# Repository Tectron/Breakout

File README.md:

Terrible Fire Break Out Boards
=================================

* 68020 - PGA114 Breakout

You may get any PCB manufacturer to produce the board for you. The board is 2-layer. I recommend these dirtypcbs links...

http://dirtypcbs.com/view.php?share=26129&accesskey=53f7f219ee0d339a3d1a7b1910aeaeed

* 68030 - PGA128 Breakout

You may get any PCB manufacturer to produce the board for you. The board is 2-layer. I recommend these dirtypcbs links...

http://dirtypcbs.com/view.php?share=28380&accesskey=9c851266aeee43fccca2846767b09b1c

* Libraries

The terriblefire.lbr file contains the following parts :-

XC9572XL-VQ64 (unverfied)

XC95144XL-TQ100 (unverified)

MC68SEC000-QFP64 (unverfied)

These parts are free to use but come with absolutely NO WARRANTY and in many cases have not been verified. 

* Tools

The following GPL tools are available.

54600.py - (Captures the output of a 56400 series scope and writes the output to a VCD file).

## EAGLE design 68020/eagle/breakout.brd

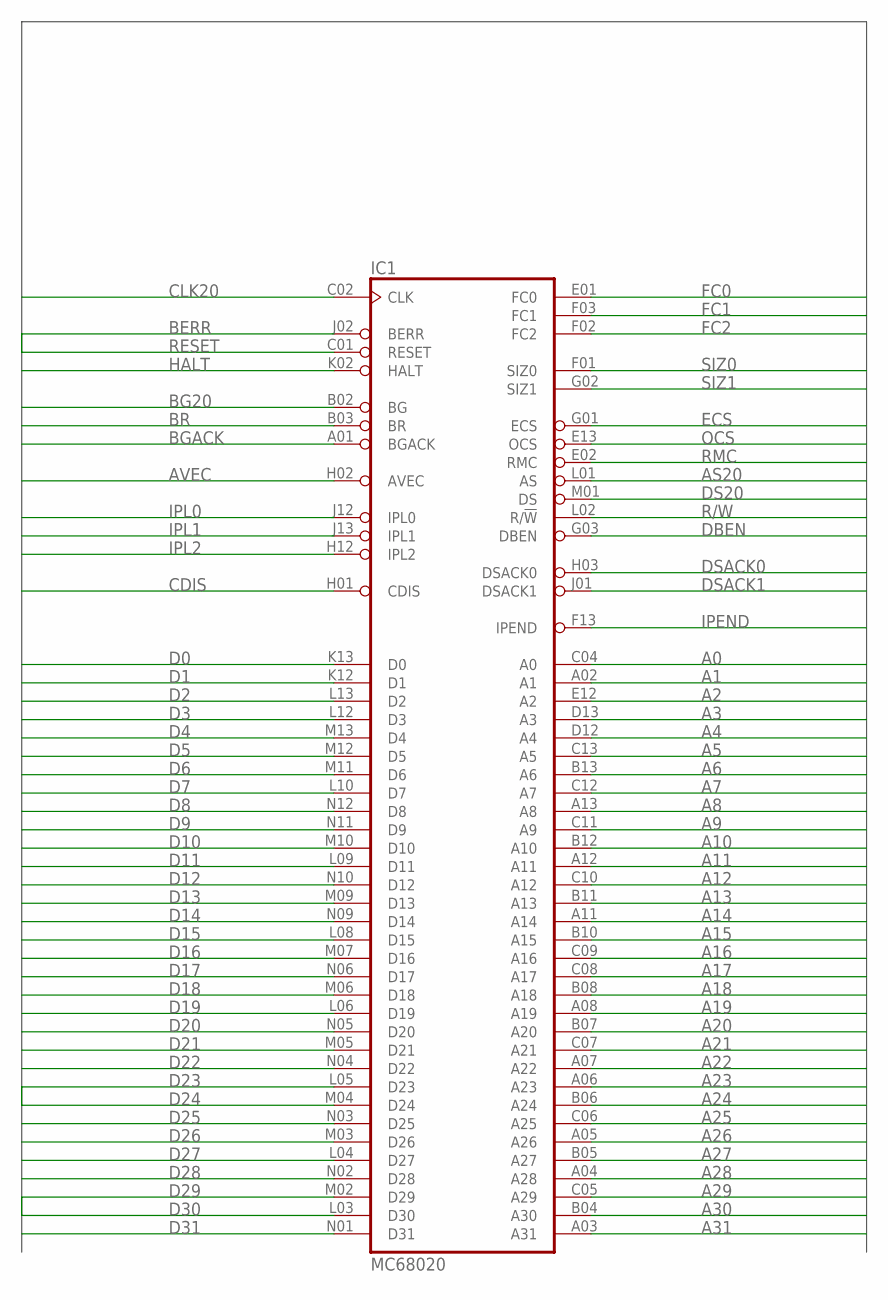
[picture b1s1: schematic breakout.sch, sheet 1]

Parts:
IC1: MC68020; MPGA114

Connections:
A0: IC1.C04 (A0); also elsewhere on the board
A1: IC1.A02 (A1); also elsewhere on the board
A2: IC1.E12 (A2); also elsewhere on the board
A3: IC1.D13 (A3); also elsewhere on the board
A4: IC1.D12 (A4); also elsewhere on the board
A5: IC1.C13 (A5); also elsewhere on the board
A6: IC1.B13 (A6); also elsewhere on the board
A7: IC1.C12 (A7); also elsewhere on the board
A8: IC1.A13 (A8); also elsewhere on the board
A9: IC1.C11 (A9); also elsewhere on the board
A10: IC1.B12 (A10); also elsewhere on the board
A11: IC1.A12 (A11); also elsewhere on the board
A12: IC1.C10 (A12); also elsewhere on the board
A13: IC1.B11 (A13); also elsewhere on the board
A14: IC1.A11 (A14); also elsewhere on the board
A15: IC1.B10 (A15); also elsewhere on the board
A16: IC1.C09 (A16); also elsewhere on the board
A17: IC1.C08 (A17); also elsewhere on the board
A18: IC1.B08 (A18); also elsewhere on the board
A19: IC1.A08 (A19); also elsewhere on the board
A20: IC1.B07 (A20); also elsewhere on the board
A21: IC1.C07 (A21); also elsewhere on the board
A22: IC1.A07 (A22); also elsewhere on the board
A23: IC1.A06 (A23); also elsewhere on the board
A24: IC1.B06 (A24); also elsewhere on the board
A25: IC1.C06 (A25); also elsewhere on the board
A26: IC1.A05 (A26); also elsewhere on the board
A27: IC1.B05 (A27); also elsewhere on the board
A28: IC1.A04 (A28); also elsewhere on the board
A29: IC1.C05 (A29); also elsewhere on the board
A30: IC1.B04 (A30); also elsewhere on the board
A31: IC1.A03 (A31); also elsewhere on the board
AS20: IC1.L01 (AS); also elsewhere on the board
AVEC: IC1.H02 (AVEC); also elsewhere on the board
BERR: IC1.J02 (BERR); also elsewhere on the board
BG20: IC1.B02 (BG); also elsewhere on the board
BGACK: IC1.A01 (BGACK); also elsewhere on the board
BR: IC1.B03 (BR); also elsewhere on the board
CDIS: IC1.H01 (CDIS); also elsewhere on the board
CLK20: IC1.C02 (CLK); also elsewhere on the board
D0: IC1.K13 (D0); also elsewhere on the board
D1: IC1.K12 (D1); also elsewhere on the board
D2: IC1.L13 (D2); also elsewhere on the board
D3: IC1.L12 (D3); also elsewhere on the board
D4: IC1.M13 (D4); also elsewhere on the board
D5: IC1.M12 (D5); also elsewhere on the board
D6: IC1.M11 (D6); also elsewhere on the board
D7: IC1.L10 (D7); also elsewhere on the board
D8: IC1.N12 (D8); also elsewhere on the board
D9: IC1.N11 (D9); also elsewhere on the board
D10: IC1.M10 (D10); also elsewhere on the board
D11: IC1.L09 (D11); also elsewhere on the board
D12: IC1.N10 (D12); also elsewhere on the board
D13: IC1.M09 (D13); also elsewhere on the board
D14: IC1.N09 (D14); also elsewhere on the board
D15: IC1.L08 (D15); also elsewhere on the board
D16: IC1.M07 (D16); also elsewhere on the board
D17: IC1.N06 (D17); also elsewhere on the board
D18: IC1.M06 (D18); also elsewhere on the board
D19: IC1.L06 (D19); also elsewhere on the board
D20: IC1.N05 (D20); also elsewhere on the board
D21: IC1.M05 (D21); also elsewhere on the board
D22: IC1.N04 (D22); also elsewhere on the board
D23: IC1.L05 (D23); also elsewhere on the board
D24: IC1.M04 (D24); also elsewhere on the board
D25: IC1.N03 (D25); also elsewhere on the board
D26: IC1.M03 (D26); also elsewhere on the board
D27: IC1.L04 (D27); also elsewhere on the board
D28: IC1.N02 (D28); also elsewhere on the board
D29: IC1.M02 (D29); also elsewhere on the board
D30: IC1.L03 (D30); also elsewhere on the board
D31: IC1.N01 (D31); also elsewhere on the board
DBEN: IC1.G03 (DBEN); also elsewhere on the board
DS20: IC1.M01 (DS); also elsewhere on the board
DSACK0: IC1.H03 (DSACK0); also elsewhere on the board
DSACK1: IC1.J01 (DSACK1); also elsewhere on the board
ECS: IC1.G01 (ECS); also elsewhere on the board
FC0: IC1.E01 (FC0); also elsewhere on the board
FC1: IC1.F03 (FC1); also elsewhere on the board
FC2: IC1.F02 (FC2); also elsewhere on the board
GND: IC1.A10 (GND), IC1.B01 (GND), IC1.B09 (GND), IC1.C03 (GND), IC1.F12 (GND), IC1.G12 (GND), IC1.H13 (GND), IC1.J03 (GND), IC1.K01 (GND), IC1.K03 (GND), IC1.L07 (GND), IC1.L11 (GND), IC1.N07 (GND); also elsewhere on the board
HALT: IC1.K02 (HALT); also elsewhere on the board
IPEND: IC1.F13 (IPEND); also elsewhere on the board
IPL0: IC1.J12 (IPL0); also elsewhere on the board
IPL1: IC1.J13 (IPL1); also elsewhere on the board
IPL2: IC1.H12 (IPL2); also elsewhere on the board
OCS: IC1.E13 (OCS); also elsewhere on the board
R/W: IC1.L02 (R/!W); also elsewhere on the board
RESET: IC1.C01 (RESET); also elsewhere on the board
RMC: IC1.E02 (RMC); also elsewhere on the board
SIZ0: IC1.F01 (SIZ0); also elsewhere on the board
SIZ1: IC1.G02 (SIZ1); also elsewhere on the board
VCC: IC1.A09 (VCC), IC1.D01 (VCC), IC1.D02 (VCC), IC1.D03 (VCC), IC1.E03 (VCC), IC1.G11 (VCC), IC1.G13 (VCC), IC1.M08 (VCC), IC1.N08 (VCC), IC1.N13 (VCC); also elsewhere on the board

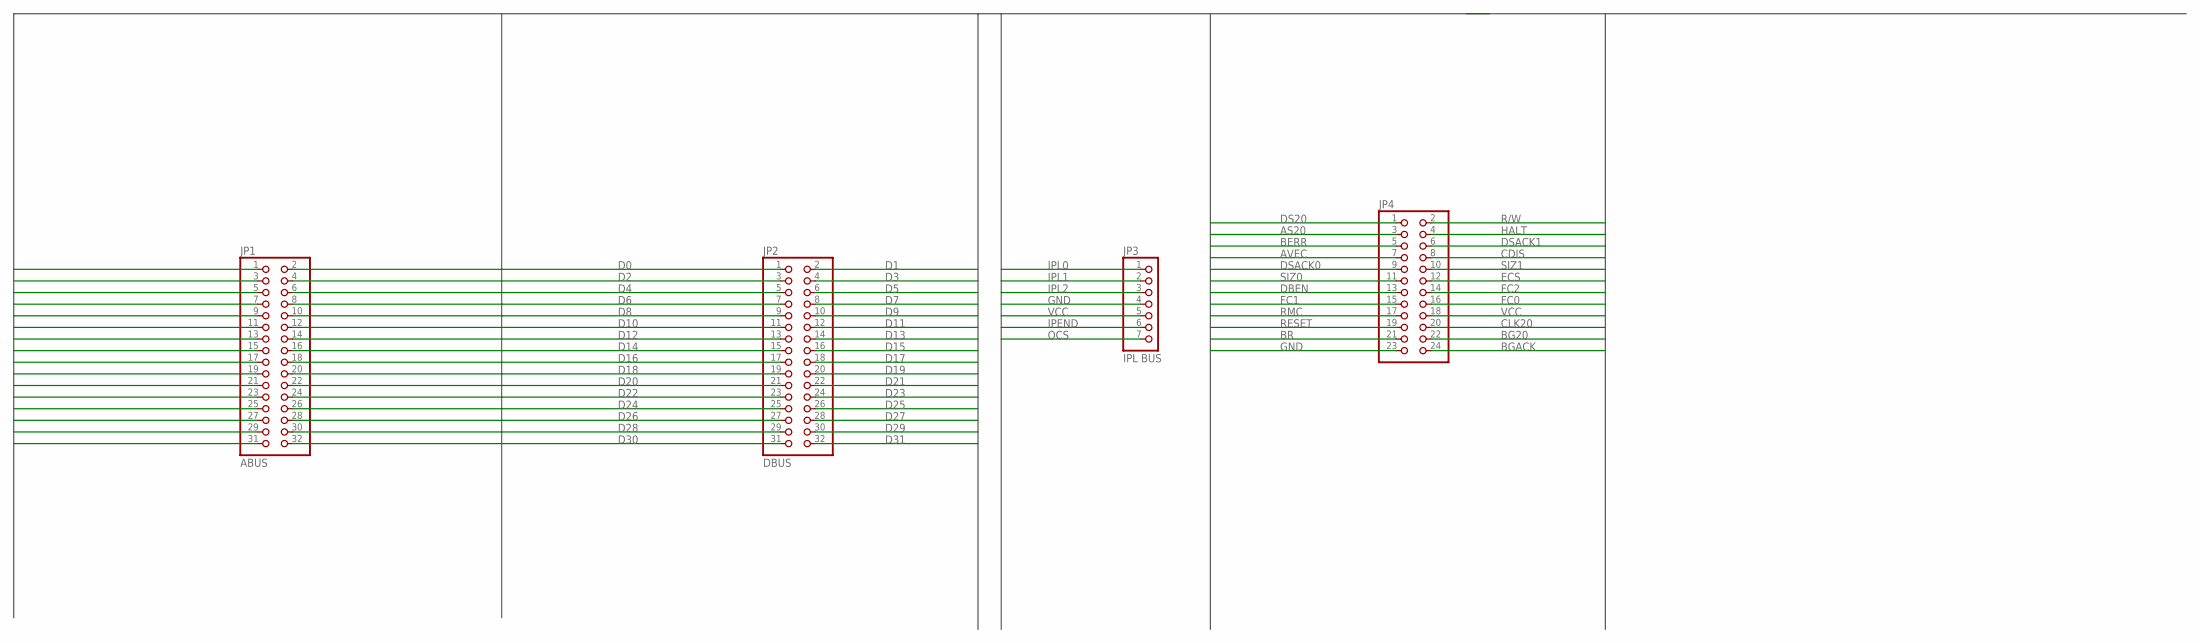
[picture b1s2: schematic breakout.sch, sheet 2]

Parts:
JP1: ABUS; 2X16
JP2: DBUS; 2X16
JP3: IPL BUS; 1X07
JP4: PINHD-2X12; 2X12

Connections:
A0: JP1.1; also elsewhere on the board
A1: JP1.2; also elsewhere on the board
A2: JP1.3; also elsewhere on the board
A3: JP1.4; also elsewhere on the board
A4: JP1.5; also elsewhere on the board
A5: JP1.6; also elsewhere on the board
A6: JP1.7; also elsewhere on the board
A7: JP1.8; also elsewhere on the board
A8: JP1.9; also elsewhere on the board
A9: JP1.10; also elsewhere on the board
A10: JP1.11; also elsewhere on the board
A11: JP1.12; also elsewhere on the board
A12: JP1.13; also elsewhere on the board
A13: JP1.14; also elsewhere on the board
A14: JP1.15; also elsewhere on the board
A15: JP1.16; also elsewhere on the board
A16: JP1.17; also elsewhere on the board
A17: JP1.18; also elsewhere on the board
A18: JP1.19; also elsewhere on the board
A19: JP1.20; also elsewhere on the board
A20: JP1.21; also elsewhere on the board
A21: JP1.22; also elsewhere on the board
A22: JP1.23; also elsewhere on the board
A23: JP1.24; also elsewhere on the board
A24: JP1.25; also elsewhere on the board
A25: JP1.26; also elsewhere on the board
A26: JP1.27; also elsewhere on the board
A27: JP1.28; also elsewhere on the board
A28: JP1.29; also elsewhere on the board
A29: JP1.30; also elsewhere on the board
A30: JP1.31; also elsewhere on the board
A31: JP1.32; also elsewhere on the board
AS20: JP4.3; also elsewhere on the board
AVEC: JP4.7; also elsewhere on the board
BERR: JP4.5; also elsewhere on the board
BG20: JP4.22; also elsewhere on the board
BGACK: JP4.24; also elsewhere on the board
BR: JP4.21; also elsewhere on the board
CDIS: JP4.8; also elsewhere on the board
CLK20: JP4.20; also elsewhere on the board
D0: JP2.1; also elsewhere on the board
D1: JP2.2; also elsewhere on the board
D2: JP2.3; also elsewhere on the board
D3: JP2.4; also elsewhere on the board
D4: JP2.5; also elsewhere on the board
D5: JP2.6; also elsewhere on the board
D6: JP2.7; also elsewhere on the board
D7: JP2.8; also elsewhere on the board
D8: JP2.9; also elsewhere on the board
D9: JP2.10; also elsewhere on the board
D10: JP2.11; also elsewhere on the board
D11: JP2.12; also elsewhere on the board
D12: JP2.13; also elsewhere on the board
D13: JP2.14; also elsewhere on the board
D14: JP2.15; also elsewhere on the board
D15: JP2.16; also elsewhere on the board
D16: JP2.17; also elsewhere on the board
D17: JP2.18; also elsewhere on the board
D18: JP2.19; also elsewhere on the board
D19: JP2.20; also elsewhere on the board
D20: JP2.21; also elsewhere on the board
D21: JP2.22; also elsewhere on the board
D22: JP2.23; also elsewhere on the board
D23: JP2.24; also elsewhere on the board
D24: JP2.25; also elsewhere on the board
D25: JP2.26; also elsewhere on the board
D26: JP2.27; also elsewhere on the board
D27: JP2.28; also elsewhere on the board
D28: JP2.29; also elsewhere on the board
D29: JP2.30; also elsewhere on the board
D30: JP2.31; also elsewhere on the board
D31: JP2.32; also elsewhere on the board
DBEN: JP4.13; also elsewhere on the board
DS20: JP4.1; also elsewhere on the board
DSACK0: JP4.9; also elsewhere on the board
DSACK1: JP4.6; also elsewhere on the board
ECS: JP4.12; also elsewhere on the board
FC0: JP4.16; also elsewhere on the board
FC1: JP4.15; also elsewhere on the board
FC2: JP4.14; also elsewhere on the board
GND: JP3.4, JP4.23; also elsewhere on the board
HALT: JP4.4; also elsewhere on the board
IPEND: JP3.6; also elsewhere on the board
IPL0: JP3.1; also elsewhere on the board
IPL1: JP3.2; also elsewhere on the board
IPL2: JP3.3; also elsewhere on the board
OCS: JP3.7; also elsewhere on the board
R/W: JP4.2; also elsewhere on the board
RESET: JP4.19; also elsewhere on the board
RMC: JP4.17; also elsewhere on the board
SIZ0: JP4.11; also elsewhere on the board
SIZ1: JP4.10; also elsewhere on the board
VCC: JP3.5, JP4.18; also elsewhere on the board

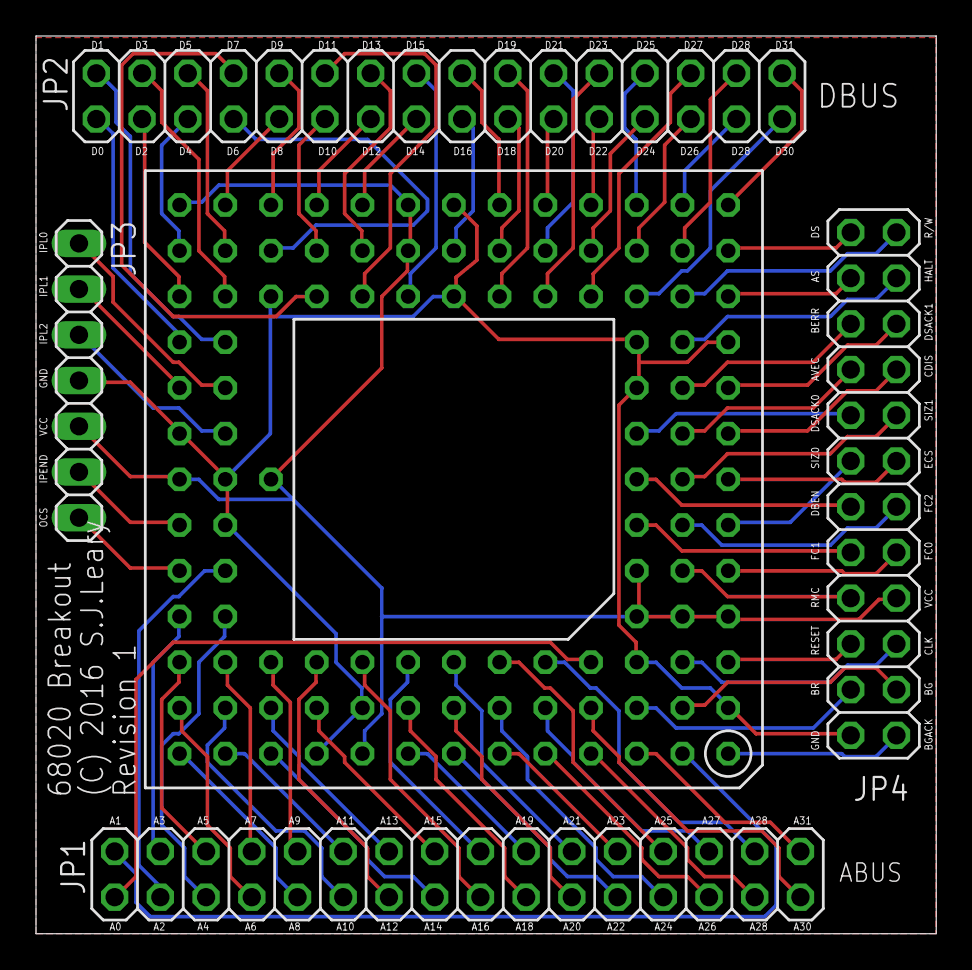
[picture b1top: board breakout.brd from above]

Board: 2 copper layers, 50.0 x 49.9 mm, 5 parts (0 on the bottom side), 93 nets.

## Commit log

2016-11-20 commiting the 68030 breakout board.
2016-11-30 Added lbrs for the XC9572XL-VQ64 and XC95144XL-TQ100
2016-12-06 added a tool for reading vcd dumps out of 54600 series scopes
2016-12-20 adding an 68SEC000 part (unverified)
2016-12-26 adding the unrouted CD32 schematic
2016-12-26 committing the cd32 breakout board schematic generation stuff.
2016-12-26 fixed the stupid Dimension outline of the CD32 connector. Bare bones routed the cd32.
2016-12-27 adding images for manufactured boards.
2016-12-27 updates.. adjusted board shape... not finished yet Added Maxim RS232 chip
2017-02-21 refactored 68020 breakout board to be a mirror of the 030 board... means they can mate. Added an unrouted shunt for the 68k
2017-03-06 Ok I routed this... :(
2017-03-09 Updates to the board files.
2017-03-09 moving these files into a new folder
2017-03-26 Create LICENSE

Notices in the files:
68020/eagle/breakout.brd:
(C) 2016 S.J.Leary
